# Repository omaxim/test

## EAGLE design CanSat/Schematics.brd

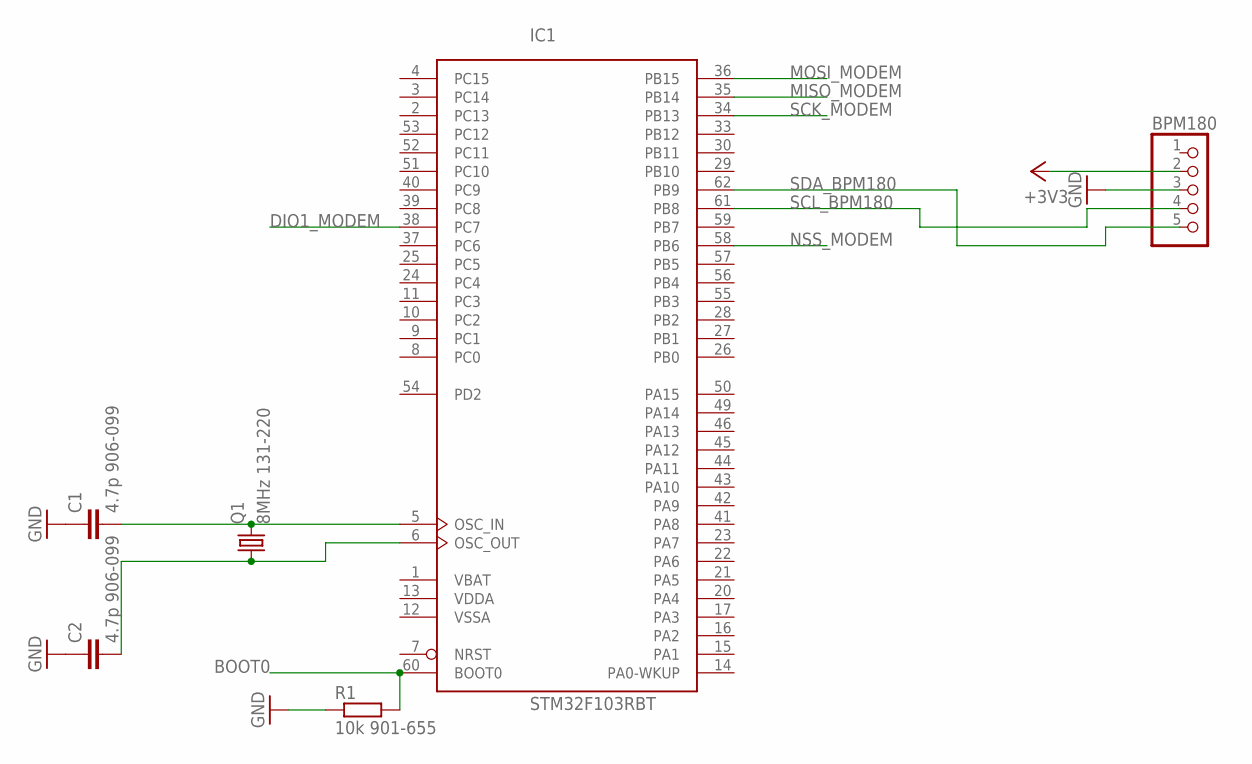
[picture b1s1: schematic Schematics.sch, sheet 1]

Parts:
BPM180: PINHD-1X5/90; 1X05/90
C1, C2: 4.7p 906-099; C0805
IC1: STM32F103RBT; LQFP64
Q1: 8MHz 131-220; HC49U-V
R1: 10k 901-655; R0805

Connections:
+3V3: BPM180.2; also elsewhere on the board
BOOT0: IC1.60 (BOOT0), R1.2
DIO1_MODEM: IC1.38 (PC7); also elsewhere on the board
GND: BPM180.3, C1.1, C2.1, R1.1; also elsewhere on the board
MISO_MODEM: IC1.35 (PB14); also elsewhere on the board
MOSI_MODEM: IC1.36 (PB15); also elsewhere on the board
unnamed: C1.2, IC1.5 (OSC_IN), Q1.2
unnamed: C2.2, IC1.6 (OSC_OUT), Q1.1
NSS_MODEM: IC1.58 (PB6); also elsewhere on the board
SCK_MODEM: IC1.34 (PB13); also elsewhere on the board
SCL_BPM180: BPM180.4, IC1.61 (PB8)
SDA_BPM180: BPM180.5, IC1.62 (PB9)
VBAT: IC1.1 (VBAT)
VDD: IC1.19 (VDD), IC1.32 (VDD), IC1.48 (VDD), IC1.64 (VDD)
VDDA: IC1.13 (VDDA)
VSS: IC1.18 (VSS), IC1.31 (VSS), IC1.47 (VSS), IC1.63 (VSS)
VSSA: IC1.12 (VSSA)

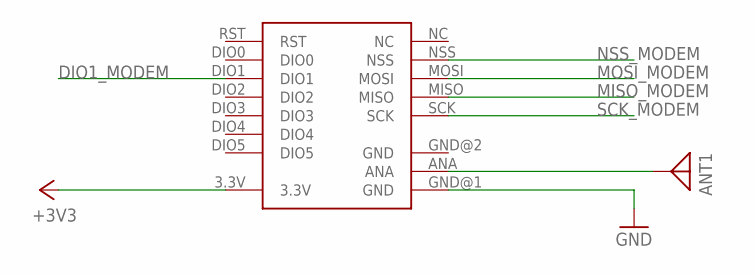
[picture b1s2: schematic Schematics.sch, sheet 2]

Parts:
ANT1: ANTENNA; PAD-01
U$1: RFM69; 20X16BOARD

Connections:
+3V3: U$1.3.3V; also elsewhere on the board
DIO1_MODEM: U$1.DIO1; also elsewhere on the board
GND: U$1.GND@1 (GND), U$1.GND@2 (GND); also elsewhere on the board
MISO_MODEM: U$1.MISO; also elsewhere on the board
MOSI_MODEM: U$1.MOSI; also elsewhere on the board
unnamed: ANT1.1, U$1.ANA
NC: U$1.NC
NSS_MODEM: U$1.NSS; also elsewhere on the board
SCK_MODEM: U$1.SCK; also elsewhere on the board

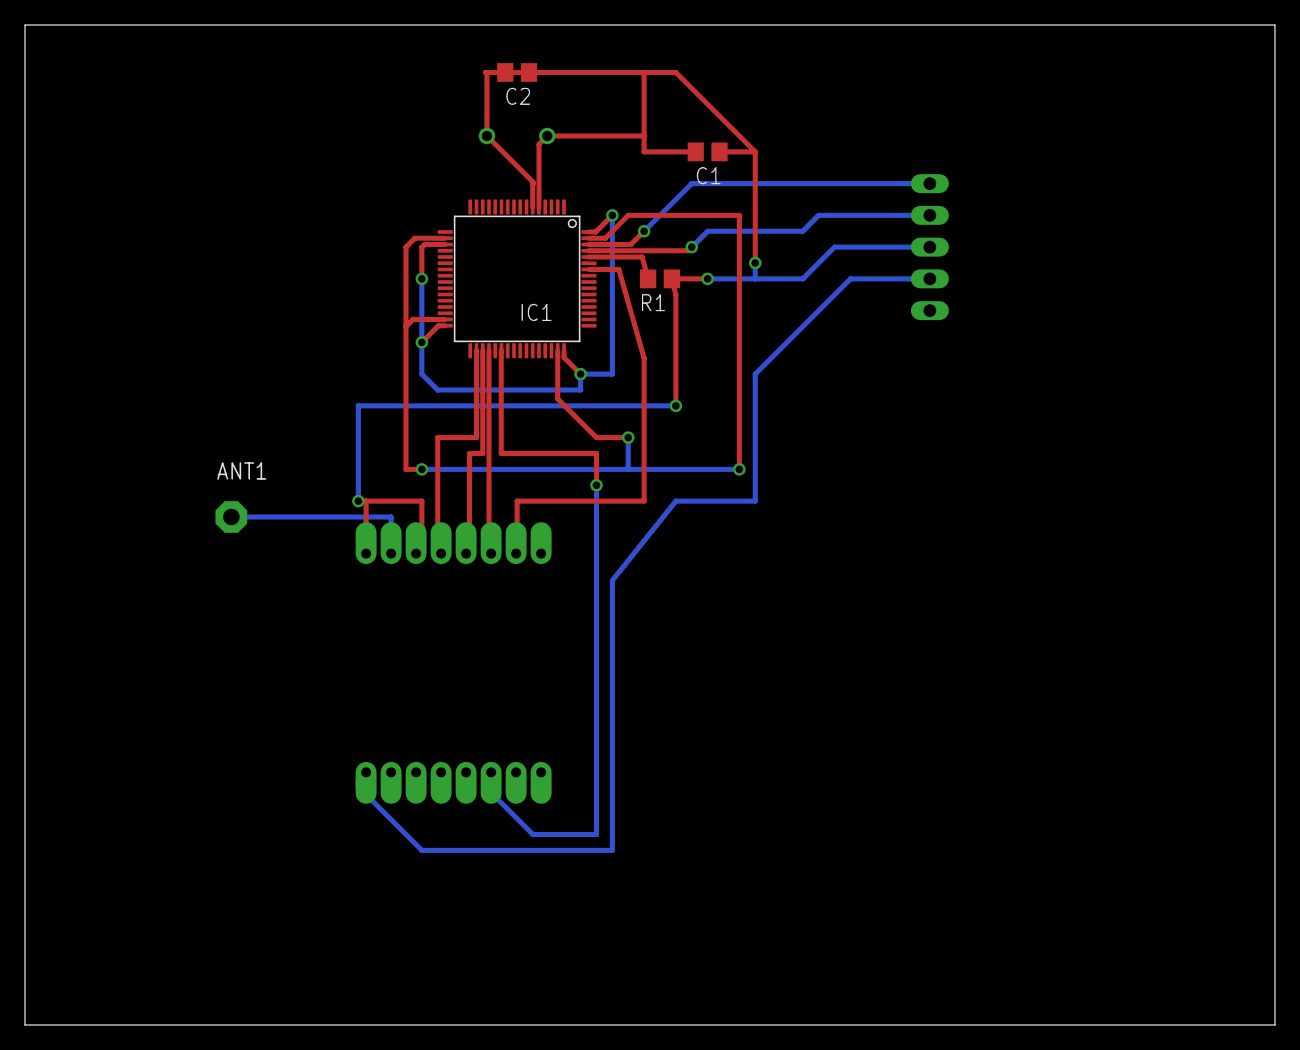
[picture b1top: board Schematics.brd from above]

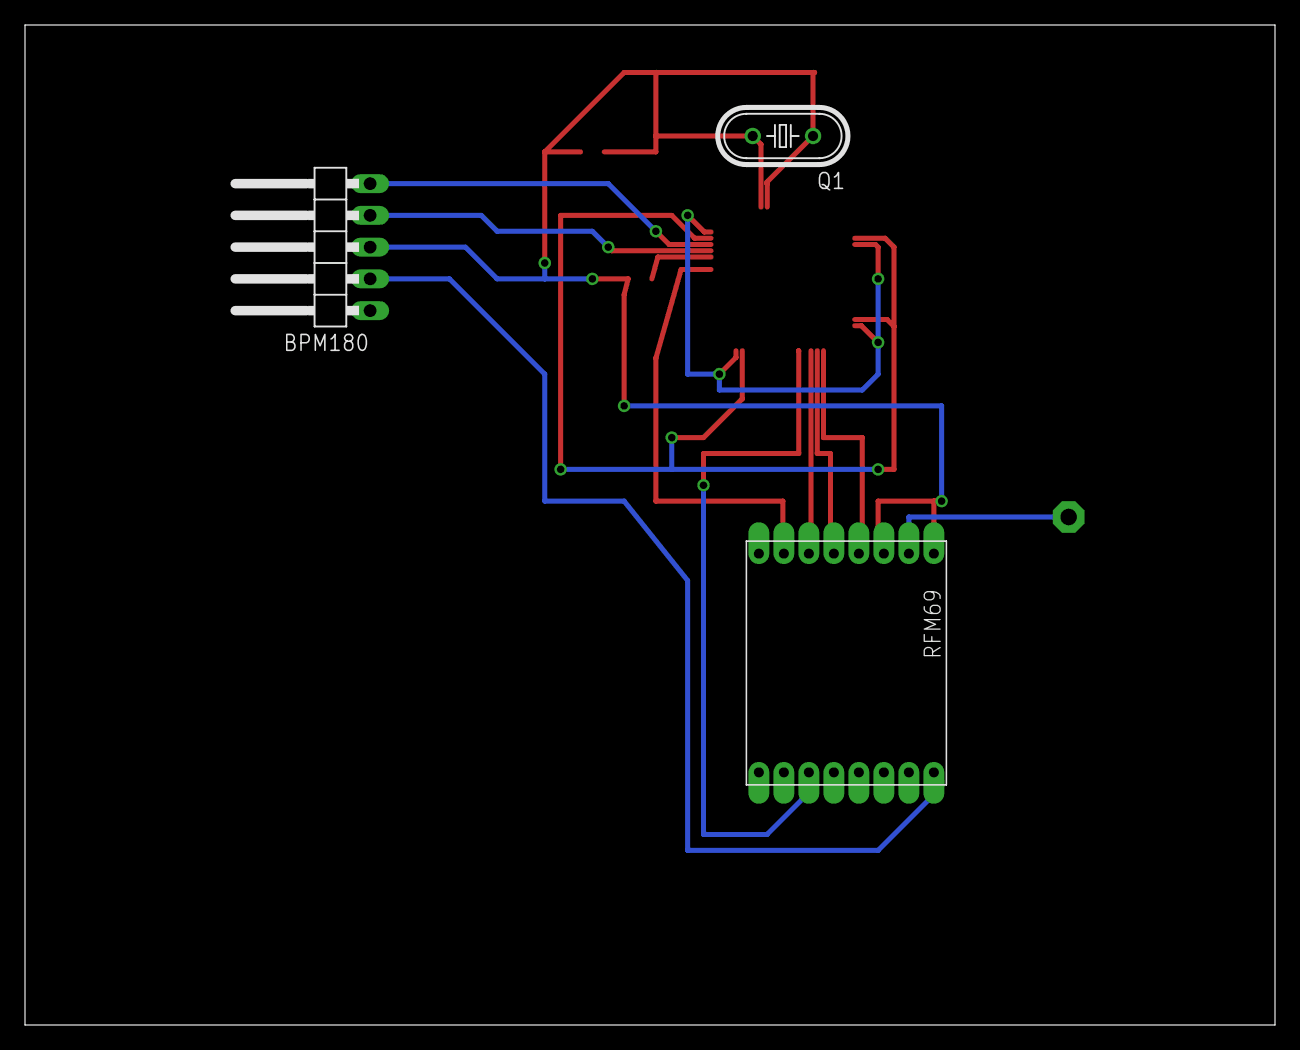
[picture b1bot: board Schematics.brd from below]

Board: 2 copper layers, 100.0 x 80.0 mm, 8 parts (3 on the bottom side), 15 nets.

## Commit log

2017-01-29 Eagle first tests
